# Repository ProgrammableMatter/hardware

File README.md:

Particle Hardware Repository
----------------------------
Hardware development repository for the particle and related hardware.

## Folder content
* **pcb-projects**: pcb projects
* **freecad**: 3D Models drawn with [FreeCAD](http://www.freecadweb.org/)
* **reflow**: reflow soldering logs, charts and helper

## PCB Projects/Versions
### Particle Version 1.21
|   |   |   |
|---|---|---|
|  |  |  |
| plugable particle with leads | pluggable particle | grid board illustartion |

### Particle version 1.1

|   |   |   | 
|---|---|---|
||||
| single particle | array example | array header |
|  | | | 
| array tail | | |

### Particle version 0.9
|   |
|---|
||
| chain example |

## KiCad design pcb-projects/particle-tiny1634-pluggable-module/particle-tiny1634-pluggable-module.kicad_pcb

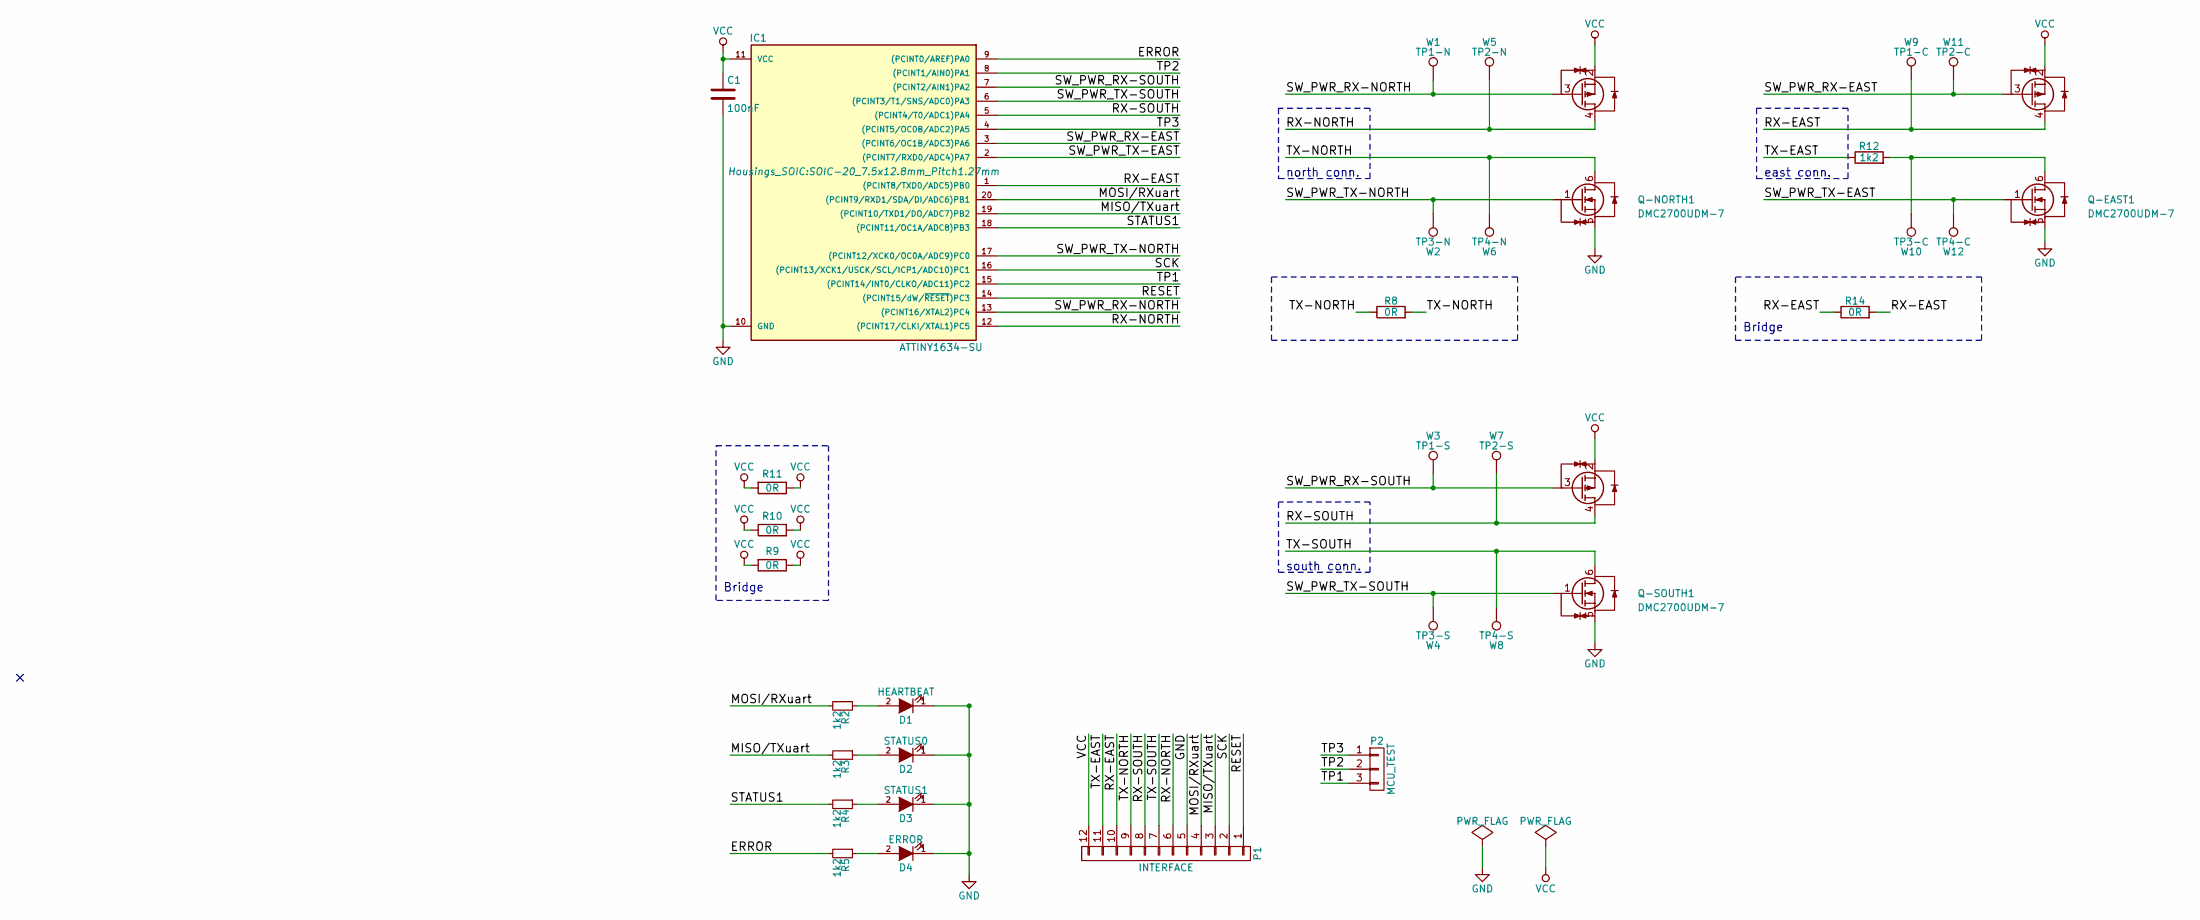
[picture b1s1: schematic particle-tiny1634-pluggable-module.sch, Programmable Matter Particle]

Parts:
C1: 100nF; C_1206_HandSoldering
D1: HEARTBEAT; R_1206_HandSoldering
D2: STATUS0; R_1206_HandSoldering
D3: STATUS1; R_1206_HandSoldering
D4: ERROR; R_1206_HandSoldering
IC1: ATTINY1634-SU; SOIC-20_7.5x12.8mm_Pitch1.27mm
P1: INTERFACE; 01x12-FCI-71607-312LF
P2: MCU_TEST; CONN-1x3
Q-EAST1: DMC2700UDM-7; SOT-26
Q-NORTH1: DMC2700UDM-7; SOT-26
Q-SOUTH1: DMC2700UDM-7; SOT-26
R2, R3, R4, R5, R12: 1k2; R_1206_HandSoldering
R8, R9, R10, R11, R14: 0R; R_1206_HandSoldering
W1: TP1-N; Measurement_Point_Square-SMD-Pad_Small
W2: TP3-N; Measurement_Point_Square-SMD-Pad_Small
W3: TP1-S; Measurement_Point_Square-SMD-Pad_Small
W4: TP3-S; Measurement_Point_Square-SMD-Pad_Small
W5: TP2-N; Measurement_Point_Square-SMD-Pad_Small
W6: TP4-N; Measurement_Point_Square-SMD-Pad_Small
W7: TP2-S; Measurement_Point_Square-SMD-Pad_Small
W8: TP4-S; Measurement_Point_Square-SMD-Pad_Small
W9: TP1-C; Measurement_Point_Square-SMD-Pad_Small
W10: TP3-C; Measurement_Point_Square-SMD-Pad_Small
W11: TP2-C; Measurement_Point_Square-SMD-Pad_Small
W12: TP4-C; Measurement_Point_Square-SMD-Pad_Small

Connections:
/ERROR: IC1.9 ((PCINT0/AREF)PA0), R5.2
/MISO/TXuart: IC1.19 ((PCINT10/TXD1/DO/ADC7)PB2), P1.3, R3.2
/MOSI/RXuart: IC1.20 ((PCINT9/RXD1/SDA/DI/ADC6)PB1), P1.4, R2.2
/RESET: IC1.14 ((PCINT15/dW/~RESET~)PC3), P1.1
/RX-EAST: IC1.1 ((PCINT8/TXD0/ADC5)PB0), P1.10, Q-EAST1.4 (D2), R14.1, R14.2, W9.1
/RX-NORTH: IC1.12 ((PCINT17/CLKI/XTAL1)PC5), P1.6, Q-NORTH1.4 (D2), W5.1
/RX-SOUTH: IC1.5 ((PCINT4/T0/ADC1)PA4), P1.8, Q-SOUTH1.4 (D2), W7.1
/SCK: IC1.16 ((PCINT13/XCK1/USCK/SCL/ICP1/ADC10)PC1), P1.2
/STATUS1: IC1.18 ((PCINT11/OC1A/ADC8)PB3), R4.2
/SW_PWR_RX-EAST: IC1.3 ((PCINT6/OC1B/ADC3)PA6), Q-EAST1.3 (G2), W11.1
/SW_PWR_RX-NORTH: IC1.13 ((PCINT16/XTAL2)PC4), Q-NORTH1.3 (G2), W1.1
/SW_PWR_RX-SOUTH: IC1.7 ((PCINT2/AIN1)PA2), Q-SOUTH1.3 (G2), W3.1
/SW_PWR_TX-EAST: IC1.2 ((PCINT7/RXD0/ADC4)PA7), Q-EAST1.1 (G1), W12.1
/SW_PWR_TX-NORTH: IC1.17 ((PCINT12/XCK0/OC0A/ADC9)PC0), Q-NORTH1.1 (G1), W2.1
/SW_PWR_TX-SOUTH: IC1.6 ((PCINT3/T1/SNS/ADC0)PA3), Q-SOUTH1.1 (G1), W4.1
/TP1: IC1.15 ((PCINT14/INT0/CLKO/ADC11)PC2), P2.3
/TP2: IC1.8 ((PCINT1/AIN0)PA1), P2.2
/TP3: IC1.4 ((PCINT5/OC0B/ADC2)PA5), P2.1
/TX-EAST: P1.11, R12.1
/TX-NORTH: P1.9, Q-NORTH1.6 (D1), R8.1, R8.2, W6.1
/TX-SOUTH: P1.7, Q-SOUTH1.6 (D1), W8.1
GND: C1.2, D1.1 (K), D2.1 (K), D3.1 (K), D4.1 (K), IC1.10 (GND), P1.5, Q-EAST1.5 (S1), Q-NORTH1.5 (S1), Q-SOUTH1.5 (S1)
unnamed: D1.2 (A), R2.1
unnamed: D2.2 (A), R3.1
unnamed: D3.2 (A), R4.1
unnamed: D4.2 (A), R5.1
unnamed: Q-EAST1.6 (D1), R12.2, W10.1
VCC: C1.1, IC1.11 (VCC), P1.12, Q-EAST1.2 (S2), Q-NORTH1.2 (S2), Q-SOUTH1.2 (S2), R9.1, R9.2, R10.1, R10.2, R11.1, R11.2

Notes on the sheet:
Bridge
north conn.
south conn.
east conn.

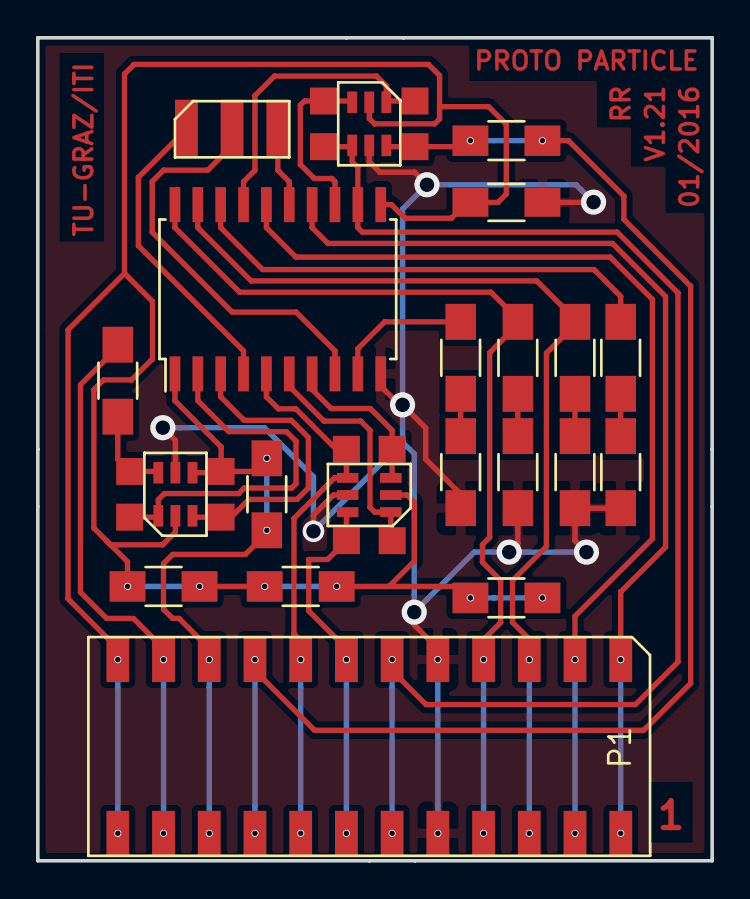
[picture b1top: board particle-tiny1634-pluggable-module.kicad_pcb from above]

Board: 2 copper layers, 37.5 x 45.7 mm, 33 parts (0 on the bottom side), 28 nets.

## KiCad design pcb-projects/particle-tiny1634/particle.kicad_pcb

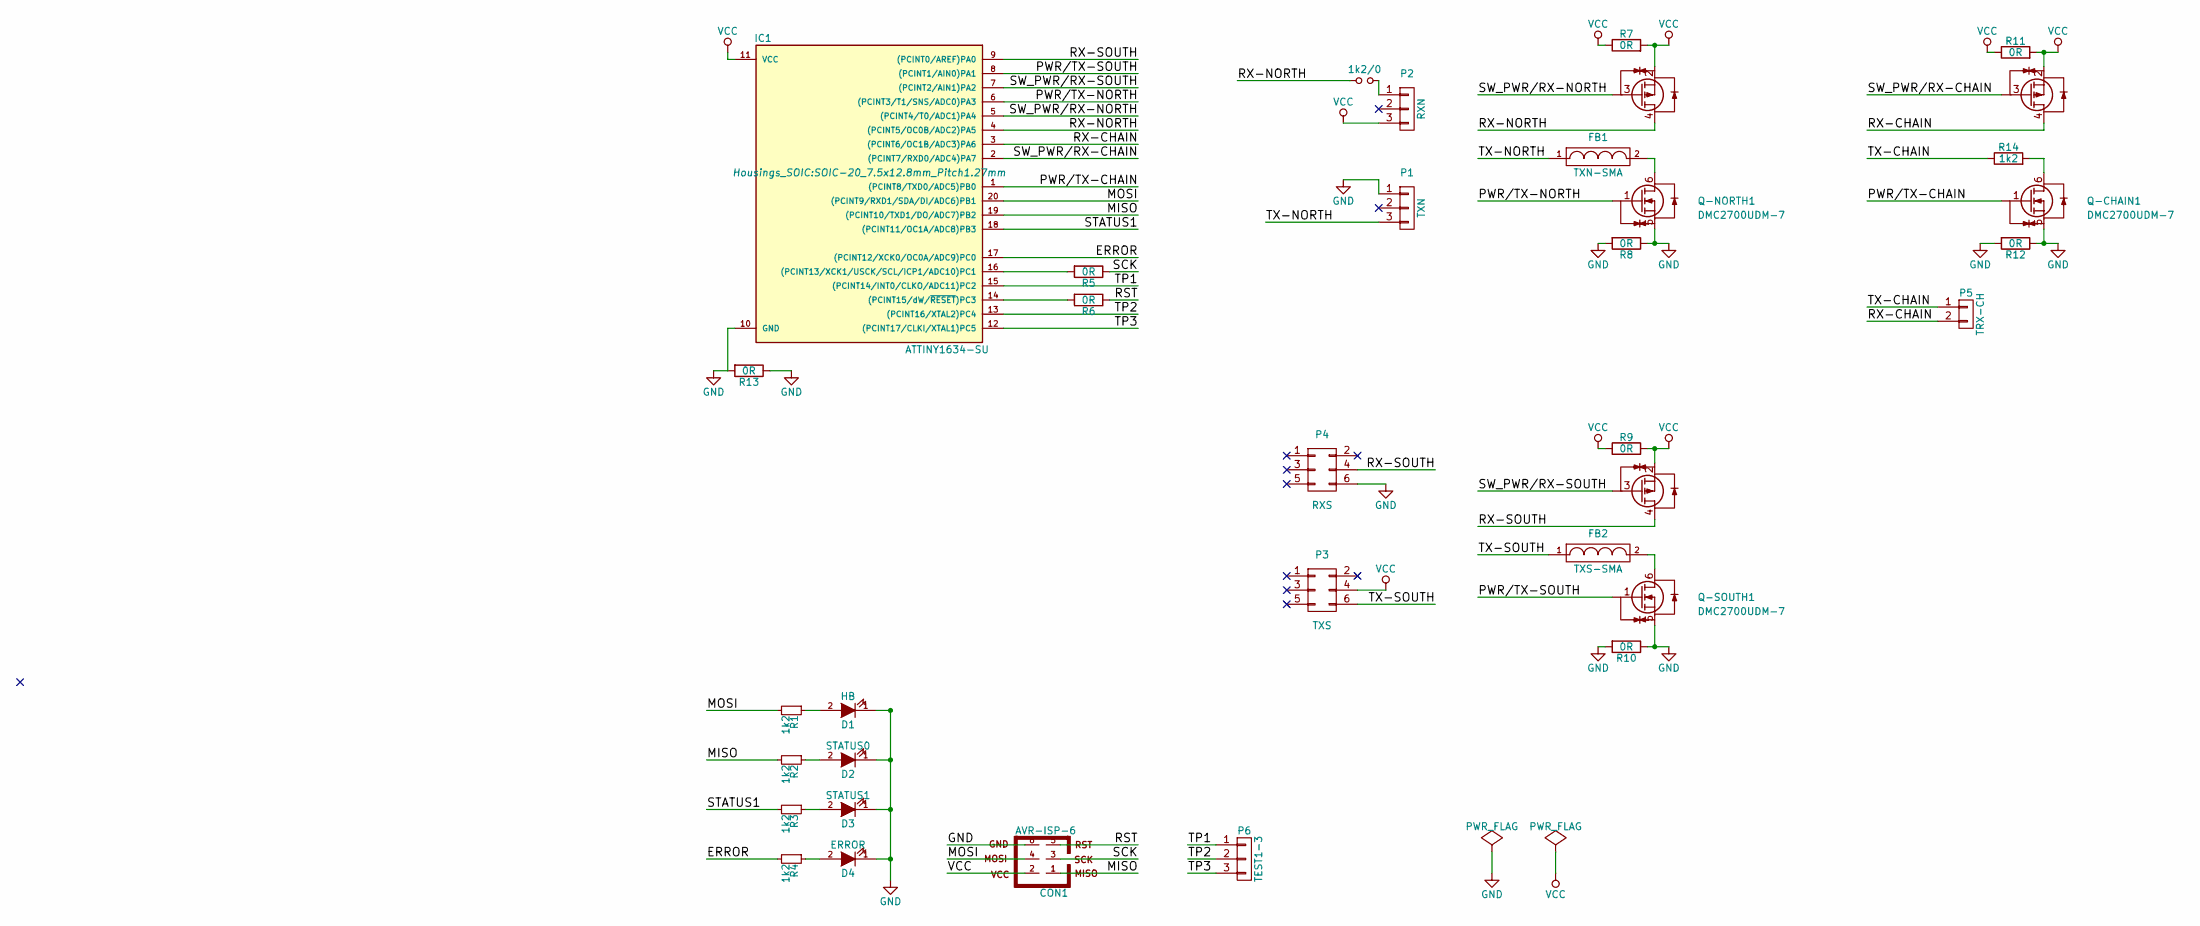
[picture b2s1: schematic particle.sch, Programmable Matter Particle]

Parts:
1k2/0: 1k2; R_1206
CON1: AVR-ISP-6; CONN-6
D1: HB; R_1206_HandSoldering
D2: STATUS0; R_1206_HandSoldering
D3: STATUS1; R_1206_HandSoldering
D4: ERROR; R_1206_HandSoldering
FB1: TXN-SMA; SMD-1206_Pol
FB2: TXS-SMA; SMD-1206_Pol
IC1: ATTINY1634-SU; SOIC-20_7.5x12.8mm_Pitch1.27mm
P1: TXN; CONN-6_1-3
P2: RXN; CONN-6_1-3
P3: TXS; CONN-6_4-6
P4: RXS; CONN-6_4-6
P5: TRX-CH; CONN-1x2
P6: TEST1-3; CONN-1x3
Q-CHAIN1: DMC2700UDM-7; SOT-26
Q-NORTH1: DMC2700UDM-7; SOT-26
Q-SOUTH1: DMC2700UDM-7; SOT-26
R1, R2, R3, R4, R14: 1k2; R_1206_HandSoldering
R5, R6, R7, R8, R9, R10, R11, R12, R13: 0R; R_1206_HandSoldering

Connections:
/ERROR: IC1.17 ((PCINT12/XCK0/OC0A/ADC9)PC0), R4.2
/MISO: CON1.1, IC1.19 ((PCINT10/TXD1/DO/ADC7)PB2), R2.2
/MOSI: CON1.4, IC1.20 ((PCINT9/RXD1/SDA/DI/ADC6)PB1), R1.2
/PWR/TX-CHAIN: IC1.1 ((PCINT8/TXD0/ADC5)PB0), Q-CHAIN1.1 (G1)
/PWR/TX-NORTH: IC1.6 ((PCINT3/T1/SNS/ADC0)PA3), Q-NORTH1.1 (G1)
/PWR/TX-SOUTH: IC1.8 ((PCINT1/AIN0)PA1), Q-SOUTH1.1 (G1)
/RST: CON1.5, R6.1
/RX-CHAIN: IC1.3 ((PCINT6/OC1B/ADC3)PA6), P5.2, Q-CHAIN1.4 (D2)
/RX-NORTH: 1k2/0.1, IC1.4 ((PCINT5/OC0B/ADC2)PA5), Q-NORTH1.4 (D2)
/RX-SOUTH: IC1.9 ((PCINT0/AREF)PA0), P4.4, Q-SOUTH1.4 (D2)
/SCK: CON1.3, R5.1
/STATUS1: IC1.18 ((PCINT11/OC1A/ADC8)PB3), R3.2
/SW_PWR/RX-CHAIN: IC1.2 ((PCINT7/RXD0/ADC4)PA7), Q-CHAIN1.3 (G2)
/SW_PWR/RX-NORTH: IC1.5 ((PCINT4/T0/ADC1)PA4), Q-NORTH1.3 (G2)
/SW_PWR/RX-SOUTH: IC1.7 ((PCINT2/AIN1)PA2), Q-SOUTH1.3 (G2)
/TP1: IC1.15 ((PCINT14/INT0/CLKO/ADC11)PC2), P6.1
/TP2: IC1.13 ((PCINT16/XTAL2)PC4), P6.2
/TP3: IC1.12 ((PCINT17/CLKI/XTAL1)PC5), P6.3
/TX-CHAIN: P5.1, R14.1
/TX-NORTH: FB1.1, P1.3
/TX-SOUTH: FB2.1, P3.6
GND: CON1.6, D1.1 (K), D2.1 (K), D3.1 (K), D4.1 (K), IC1.10 (GND), P1.1, P4.6, Q-CHAIN1.5 (S1), Q-NORTH1.5 (S1), Q-SOUTH1.5 (S1), R8.1, R8.2, R10.1, R10.2, R12.1, R12.2, R13.1, R13.2
unnamed: 1k2/0.2, P2.1
unnamed: D1.2 (A), R1.1
unnamed: D2.2 (A), R2.1
unnamed: D3.2 (A), R3.1
unnamed: D4.2 (A), R4.1
unnamed: FB1.2, Q-NORTH1.6 (D1)
unnamed: FB2.2, Q-SOUTH1.6 (D1)
unnamed: IC1.14 ((PCINT15/dW/~RESET~)PC3), R6.2
unnamed: IC1.16 ((PCINT13/XCK1/USCK/SCL/ICP1/ADC10)PC1), R5.2
unnamed: Q-CHAIN1.6 (D1), R14.2
VCC: CON1.2, IC1.11 (VCC), P2.3, P3.4, Q-CHAIN1.2 (S2), Q-NORTH1.2 (S2), Q-SOUTH1.2 (S2), R7.1, R7.2, R9.1, R9.2, R11.1, R11.2

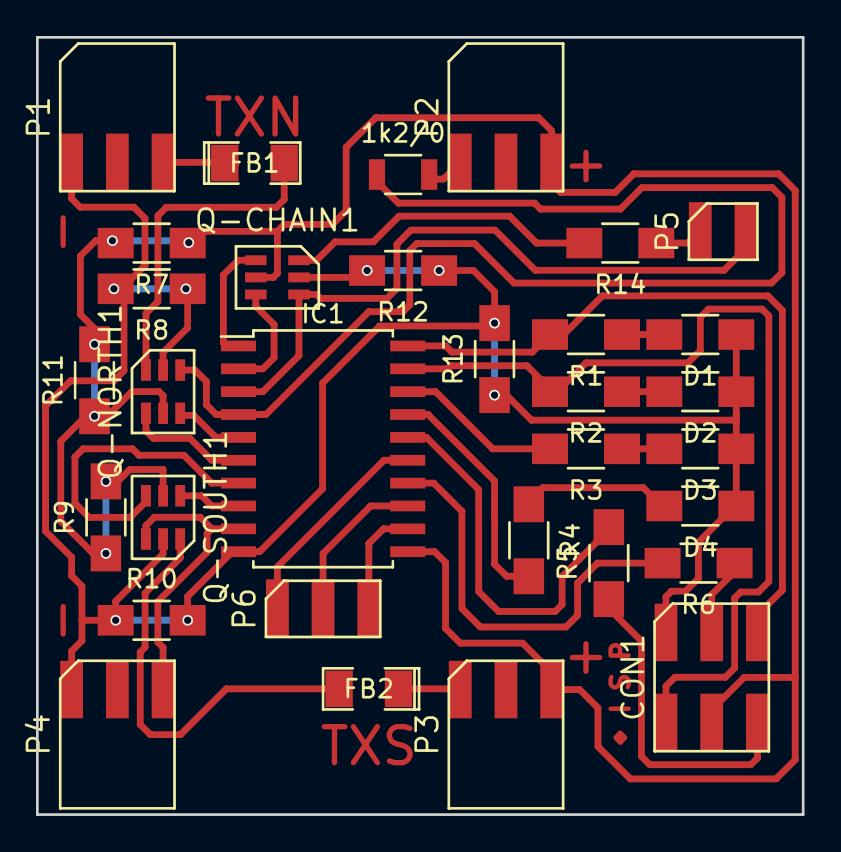
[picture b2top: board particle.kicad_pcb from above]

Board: 2 copper layers, 42.5 x 43.2 mm, 32 parts (0 on the bottom side), 33 nets.

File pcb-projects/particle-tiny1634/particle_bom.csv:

Reference, Value, supplyer, price,needed pcs,needed pcs/pkg,Price / entity,price total,
CON1,AVR-ISP-6,http://at.rs-online.com/web/p/leiterplatten-header/5286417/,2row-20pole-10pcs/pkg  10-40pcs 2.177,6pcs for 8,1,"2,177","2,177",
D1,HB,http://at.rs-online.com/web/p/leds-sichtbares-licht/7269225/,25-100pcs 0.154,1x8,8,"0,154","1,232",
D2,STATUS0,http://at.rs-online.com/web/p/leds-sichtbares-licht/7269215/,25-100pcs 0.14,2x8,16,"0,14","2,24",
D4,ERROR,http://at.rs-online.com/web/p/leds-sichtbares-licht/7269212/,25-100pcs 0.197 ,1x8,8,"0,197","1,576",
FB1,TXN-SMA,http://at.rs-online.com/web/p/anzeigen-gluehlampen/0106458/,<240pcs 0.733,2x8,16,"0,733","11,728",
IC1,ATTINY1634-SU,http://at.rs-online.com/web/p/mikrocontroller/7617703/,rs attiny1634R-su 2-8pcs 1.84 >10pcs 1.725 farnell attiny1634-su <10pcs 1.44 <25pcs 1.35,1x8,8,"1,84","14,72",
P6,TEST1-3,http://at.rs-online.com/web/p/leiterplatten-header/0155901/,5pcs-40pol/pkg pcs 1.324,1.6pcs,1,"6,6","6,6",
Q-NORTH1,DMC2700UDM-7,http://at.rs-online.com/web/p/transistoren-mosfet/8232918/,20-80pcs 0.1291 >100pcs 0.132,2x8+2,18,"0,132","2,376",
R14,1k2,http://at.rs-online.com/web/p/smd-widerstande/8071158/,< 5pkg @ 100pcs 1.72 per pkg,5x8,1,"1,7","1,7",
,,http://at.rs-online.com/web/p/smd-widerstande/7409104/,<450pcs 0.016,7x8+2x2,60,"0,016","0,96",
,,,,,,,"45,309", = total sum
,,,,,,,,
,,,,,,,,
,usb a smd,http://at.farnell.com/multicomp/usb-a-s-ra-tsmt/usb-3-0-buch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,"< 50pcs 0,578",1,10,"0,578","5,8",

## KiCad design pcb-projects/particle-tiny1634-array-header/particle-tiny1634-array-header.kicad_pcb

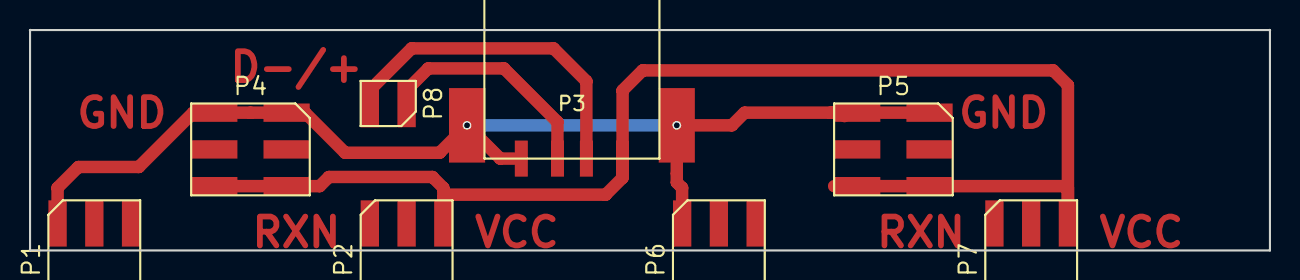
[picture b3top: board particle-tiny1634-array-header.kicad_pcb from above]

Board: 2 copper layers, 85.7 x 15.2 mm, 8 parts (0 on the bottom side), 4 nets.

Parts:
P1: CHAIN1-TX; CONN-6_4-6
P2: CHAIN1-RX; CONN-6_4-6
P3: USB_A; usb-30-right-angle-true-smt
P4: PWR-WEST; CONN-6
P5: PWR-EAST; CONN-6
P6: CHAIN2-TX; CONN-6_4-6
P7: CHAIN2-RX; CONN-6_4-6
P8: RS232; CONN-1x2

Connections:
/D+: P3.3, P8.1
/D-: P3.2, P8.2
GND: P1.6, P3.4, P3.5, P4.1, P4.6, P5.1, P5.6, P6.6
VCC: P2.4, P3.1, P4.3, P4.4, P5.3, P5.4, P7.4

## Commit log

2015-01-15 added particle project
2015-01-19 added initial version of proto pcb
2015-01-20 close issue #4, close issue #8
2015-01-20 connected h-bridges to comm wires
2015-01-21 begun with tpi connector
2015-01-22 begun with routing
2015-01-23 added test pins
2015-01-23 routed bard
2015-01-23 added missing track and vcc/gnd holes
2015-01-26 replaced packages/library of attiny20 and dmc2400uv
2015-01-27 close 21, close 22
2015-01-27 fixes #13
2015-01-28 routing board
2015-01-29 close #26, close #31, close #30, close #28, close #25, close #24, close #23
2015-01-29 close #27, close #19, close #30,skip / close #18, skip / close #14
2015-01-31 renamed folder
2015-01-31 routed isp header
2015-01-31 routed board - usable version without filling in gnd/vcc fields
2015-01-31 fixed some issues, added polygons
2015-01-31 filled out vcc/gnd areas
2015-02-01 set values to all leds, renamed gnd/vcc pads, TX/RX description beside pads, placed vcc/gnd shunts exposed on schema
2015-02-01 renamed files/folder
2015-02-01 fixed typo in schema
2015-02-02 solved #34, solved #33, solved #32
2015-02-02 added several sparkfun and one samtec library, fixed #39, fixed #37, fixed #36, fixed #35, fixed #29
2015-02-03 fixed #41, fixed #40, fixed #39, fixed #37, fixed #35, fixed #29
2015-02-04 routed board after several changes to schema
2015-02-04 closed #44, closed #43, closed #42
2015-02-05 renamed parts in schema
2015-02-06 fixed #47
2015-02-08 corrected version number
2015-02-08 created library for several smt switches (rs components)
2015-02-09 routed board with rs components
2015-02-09 added missing wire
2015-02-09 cosmetics
2015-02-09 removed obsolet library folder
2015-02-10 changed 90° spi connector to straight one
2015-02-10 fixed wrong tpi/spi-switch configuration matrix on schema
2015-02-10 small modification
2015-02-10 changed all resistors 1k -> 150
2015-02-11 cosmetics: moved 5V label and testpoint 1 smome mm
2015-02-11 enhanced switch: now has 4 terminals - polygon filling now makes termal pad correct
2015-02-12 successfully connected four tiny airwires below pads
2015-02-12 last updates
2015-02-12 reduced size
2015-02-12 aligned C1
2015-02-12 tstop polygon
2015-02-19 added script for connecting and logging the reflow controller
2015-02-19 created a reflow profile for the tug oven
2015-02-20 ignoring eagle leftovers
2015-02-20 removed unnecessary file
2015-02-25 highlighted design error on schema regarding tx-leds
2015-03-01 fixed #52, fixed #53, fixed #54, fixed #57
2015-05-05 soldering oven heat curves
2015-09-28 added reflow temperature curves
2015-12-22 removed led on rx due to damping signal issue
2016-01-04 added particle sketch created with kicad
2016-01-04 deleted temp files
2016-01-04 routed attiny1634 particle
2016-01-06 re-routed smaller pcb, added several 3d packages, min. fix in schema
2016-01-06 added all 3d models, pcb cosmetics
2016-01-06 increased clearance from 0.2mm to 0.33mm
2016-01-08 added bill of material
2016-01-09 added usb connector module/3d
2016-01-10 added border to usb footprint
2016-01-10 added array header and tail
2016-01-10 removed bak files
2016-01-27 minor edge cut alignment, added particle array
2016-01-28 routed pluggable particle
2016-01-29 added board with lead
2016-01-30 run cleaned up on pcbs
2016-01-30 added euro-pcb with multiple modules placed on it
2016-01-31 remved no-net zones, refined gnd zone
2016-01-31 added power supply capacitor
2016-01-31 updated euro pcb
2016-02-01 minor change: updated MCU power supply decoupling and euro pcb
2016-02-03 removed mistakenly exported grid planes
2016-02-03 elongated leads
2016-02-03 added grid board visualization
2016-02-03 added mosfet-sma-connection example schema
2016-02-04 added grid board sketch
2016-02-04 refined grid board: cutouts
2016-02-04 restructured folder hierarchy
2016-02-04 change shape, updated euro pcb
2016-02-04 added missing symlinks
2016-02-04 updated grid board sketch
2016-02-08 grid board illustration is now in grey
2016-02-08 added particle v1.1 array
2016-07-20 changed network names slightly
2016-08-03 cleanup folders; minimal pcb changes
2016-08-03 removed redundant files
2016-08-03 renamed files
2016-08-03 removed file
2016-08-03 added readme
2016-08-03 added more images
2016-08-07 restored tx bridge example schema
